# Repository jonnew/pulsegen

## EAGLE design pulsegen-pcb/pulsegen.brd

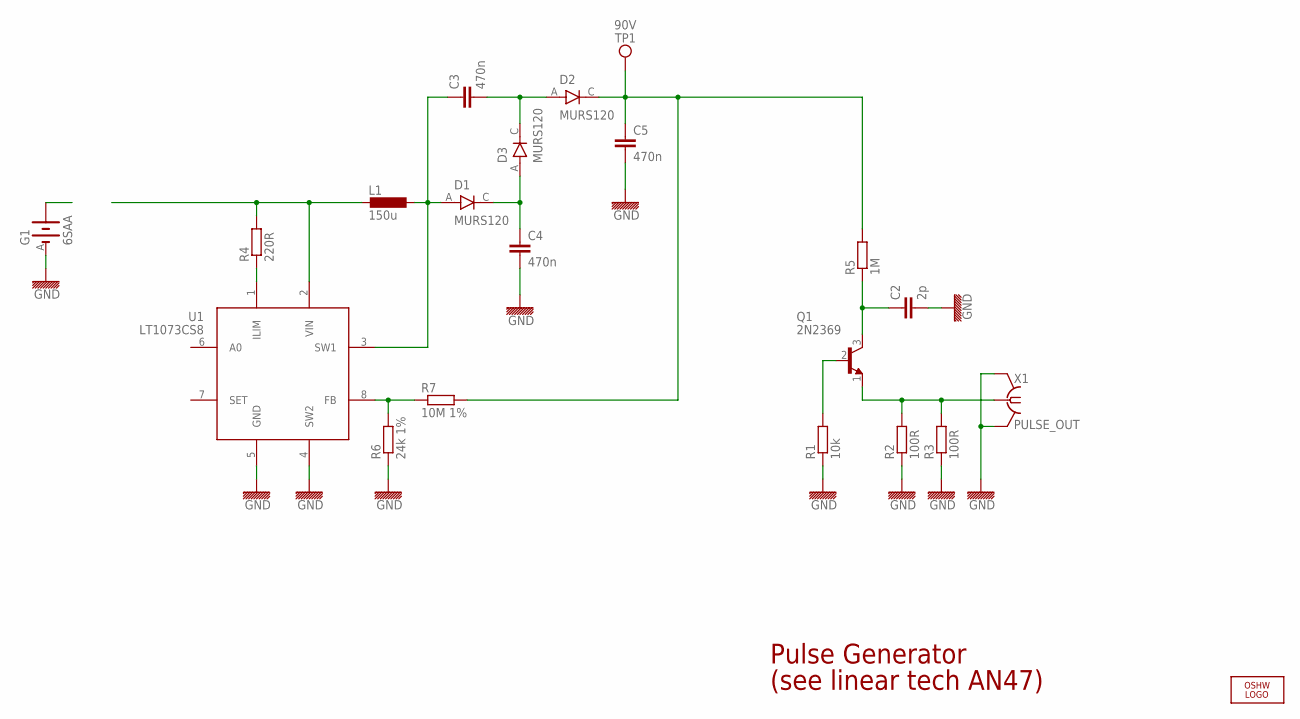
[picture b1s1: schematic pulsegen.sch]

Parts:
C2: 2p; 0805
C3, C4, C5: 470n; 1210
D1, D2, D3: MURS120; SMB_DIODE
G1: 6SAA
L1: 150u; L_WE_PD_M
LOGO1: OSHW_LOGO_FILLX0100-NT; OSHW_FILLX100_NOTEXT
Q1: 2N2369; TO18
R1: 10k; 0805
R2, R3: 100R; 0805
R4: 220R; 0805
R5: 1M; 0805
R6: 24k 1%; 0805
R7: 10M 1%; 0805
TP1: 90V; TP_1X1
U1: LT1073CS8; SO8
X1: PULSE_OUT; BNC-EDGE-BIVB

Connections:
90V: C5.1, D2.C, R5.2, R7.2, TP1.TP
BASE: Q1.2 (B), R1.2
CHARGE: C2.1, Q1.3 (C), R5.1
FB: R6.2, R7.1, U1.8 (FB)
GND: C2.2, C4.2, C5.2, G1.A, R1.1, R2.1, R3.1, R6.1, U1.4 (SW2), U1.5 (GND), X1.GND@1 (GND), X1.GND@2 (GND)
N1: C4.1, D1.C, D3.A
N2: C3.2, D2.A, D3.C
unnamed: R4.1, U1.1 (ILIM)
PULSE: Q1.1 (E), R2.2, R3.2, X1.C (1)
SW1: C3.1, D1.A, L1.1, U1.3 (SW1)
VIN: L1.2, R4.2, U1.2 (VIN)

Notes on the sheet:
Pulse Generator
(see linear tech AN47)

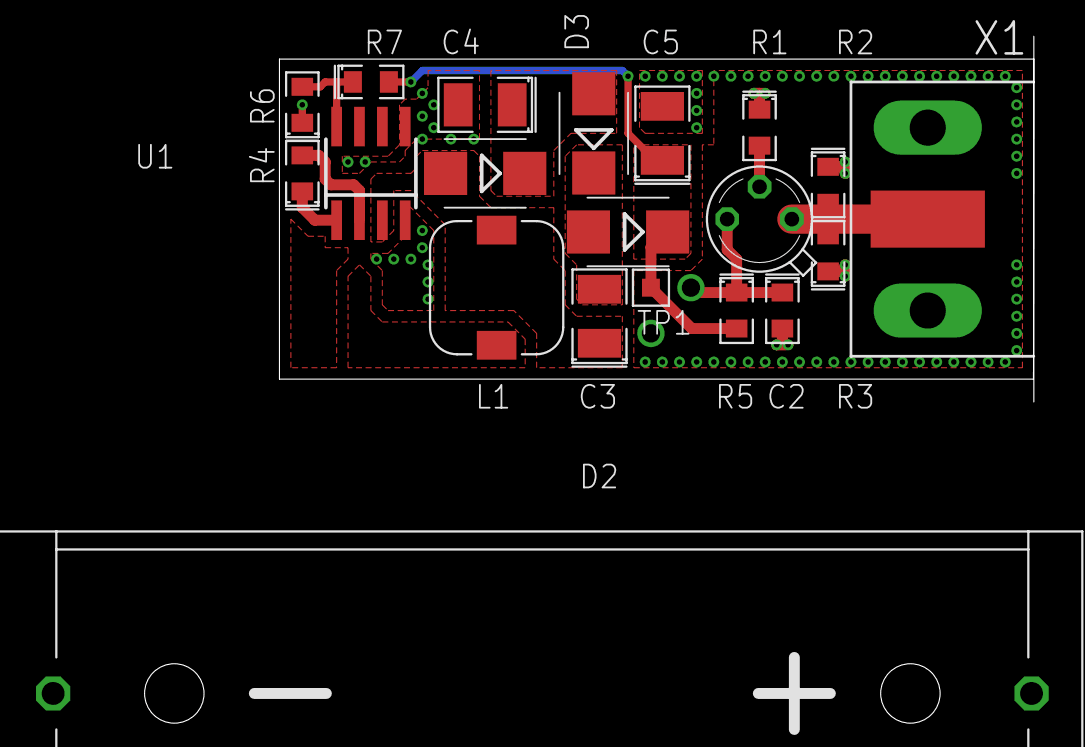
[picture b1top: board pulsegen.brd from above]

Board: 2 copper layers, 41.9 x 17.8 mm, 21 parts (1 on the bottom side), 11 nets.

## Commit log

2015-01-24 Initial commit.

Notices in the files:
pulsegen-pcb/pulsegen.brd:
(c) 2012 Munaut.S
OSHW / CC-BY-SA
